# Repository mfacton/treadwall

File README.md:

# treadwall
Electronics for lightable rotating rockwall

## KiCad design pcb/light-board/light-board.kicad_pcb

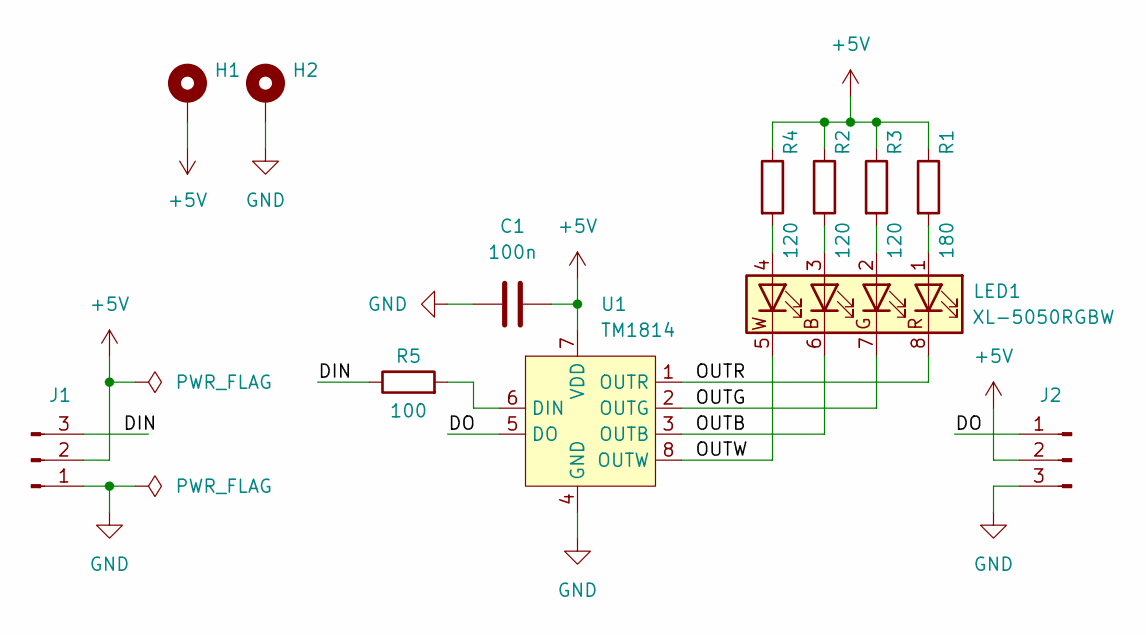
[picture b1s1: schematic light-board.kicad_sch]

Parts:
C1: 100n; C_0402_1005Metric; LCSC C1525
H1, H2: MountingHole_Pad; MountingHole_3.2mm_M3_Pad
J1, J2: Conn_01x03_Pin; JST_PH_S3B-PH-K_1x03_P2.00mm_Horizontal; LCSC C157929
LED1: XL-5050RGBW; LCSC C7371891
R1: 180; R_0603_1608Metric; LCSC C22828
R2, R3, R4: 120; R_0603_1608Metric; LCSC C22787
R5: 100; R_0402_1005Metric; LCSC C25076
U1: TM1814; SOP-8_3.9x4.9mm_P1.27mm; LCSC C20622183

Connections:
+5V: C1.2, H1.1, J1.2, J2.2, R1.1, R2.1, R3.1, R4.1, U1.7 (VDD)
/DIN: J1.3, R5.1
/DO: J2.1, U1.5 (DO)
/OUTB: LED1.6 (BK), U1.3 (OUTB)
/OUTG: LED1.7 (GK), U1.2 (OUTG)
/OUTR: LED1.8 (RK), U1.1 (OUTR)
/OUTW: LED1.5 (WK), U1.8 (OUTW)
GND: C1.1, H2.1, J1.1, J2.3, U1.4 (GND)
unnamed: LED1.3 (BA), R2.2
unnamed: LED1.2 (GA), R3.2
unnamed: LED1.1 (RA), R1.2
unnamed: LED1.4 (WA), R4.2
unnamed: R5.2, U1.6 (DIN)

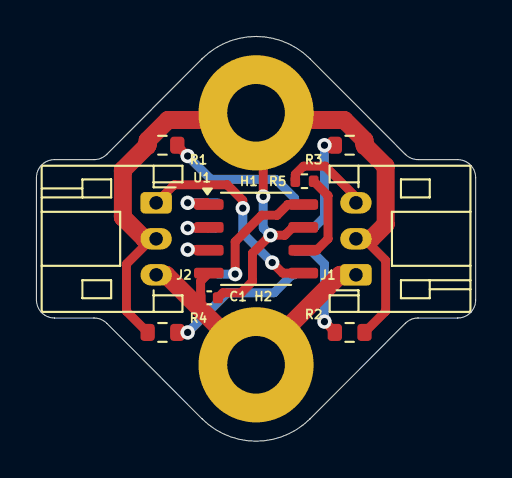
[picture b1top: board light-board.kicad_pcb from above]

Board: 2 copper layers, 24.4 x 22.5 mm, 12 parts (1 on the bottom side), 13 nets.

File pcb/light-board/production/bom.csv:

Designator,Footprint,Quantity,Value,LCSC Part #
C1,0402,1,100n,C1525
"J1, J2",JST_PH_S3B-PH-K_1x03_P2.00mm_Horizontal,2,Conn_01x03_Pin,C157929
LED1,XL-5050RGBW,1,XL-5050RGBW,C7371891
R1,0603,1,180,C22828
"R2, R3, R4",0603,3,120,C22787
R5,0402,1,100,C25076
U1,SOP-8_3.9x4.9mm_P1.27mm,1,TM1814,C20622183

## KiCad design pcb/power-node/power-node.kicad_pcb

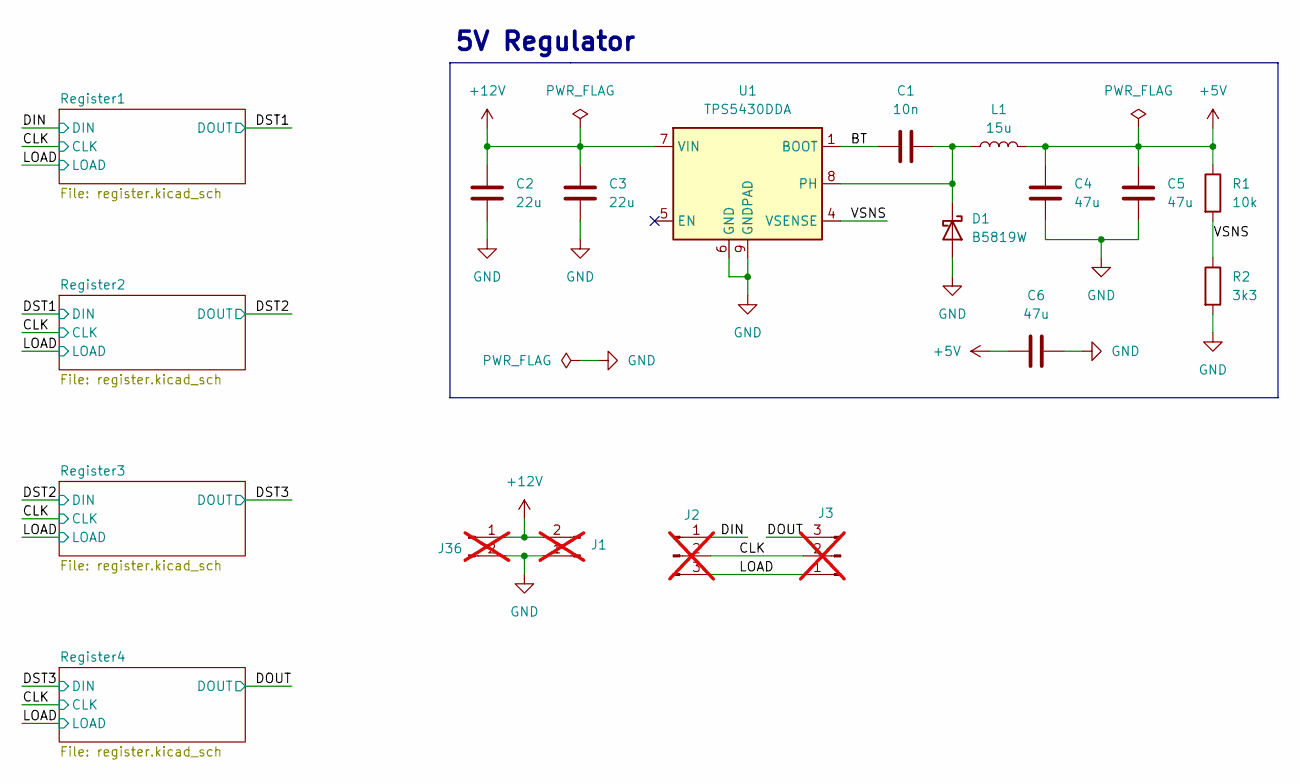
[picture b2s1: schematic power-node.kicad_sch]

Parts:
C1: 10n; C_0402_1005Metric; LCSC C15195
C2, C3: 22u; C_1206_3216Metric; LCSC C12891
C4, C5, C6: 47u; C_1206_3216Metric; LCSC C96123
D1: B5819W; D_SOD-123; LCSC C8598
J1, J36: Conn_01x02_Pin; WJ126V-5.0-2P; LCSC C8404; not fitted
J2, J3: Conn_01x03_Pin; PinHeader_1x03_P2.54mm_Vertical; not fitted
L1: 15u; L_Abracon_ASPI-0630LR; LCSC C177243
R1: 10k; R_0402_1005Metric; LCSC C25744
R2: 3k3; R_0402_1005Metric; LCSC C25890
U1: TPS5430DDA; TI_SO-PowerPAD-8_ThermalVias; LCSC C9864

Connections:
+5V: C4.1, C5.1, C6.1, L1.2, R1.1; also elsewhere on the board
+12V: C2.1, C3.1, J1.2, J36.1, U1.7 (VIN)
/BT: C1.1, U1.1 (BOOT)
/CLK: J2.2, J3.2; also elsewhere on the board
/DIN: J2.1; also elsewhere on the board
/DOUT: J3.3; also elsewhere on the board
/LOAD: J2.3, J3.1; also elsewhere on the board
/VSNS: R1.2, R2.1, U1.4 (VSENSE)
GND: C2.2, C3.2, C4.2, C5.2, C6.2, D1.2 (A), J1.1, J36.2, R2.2, U1.6 (GND), U1.9 (GNDPAD); also elsewhere on the board
unnamed: C1.2, D1.1 (K), L1.1, U1.8 (PH)

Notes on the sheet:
5V Regulator

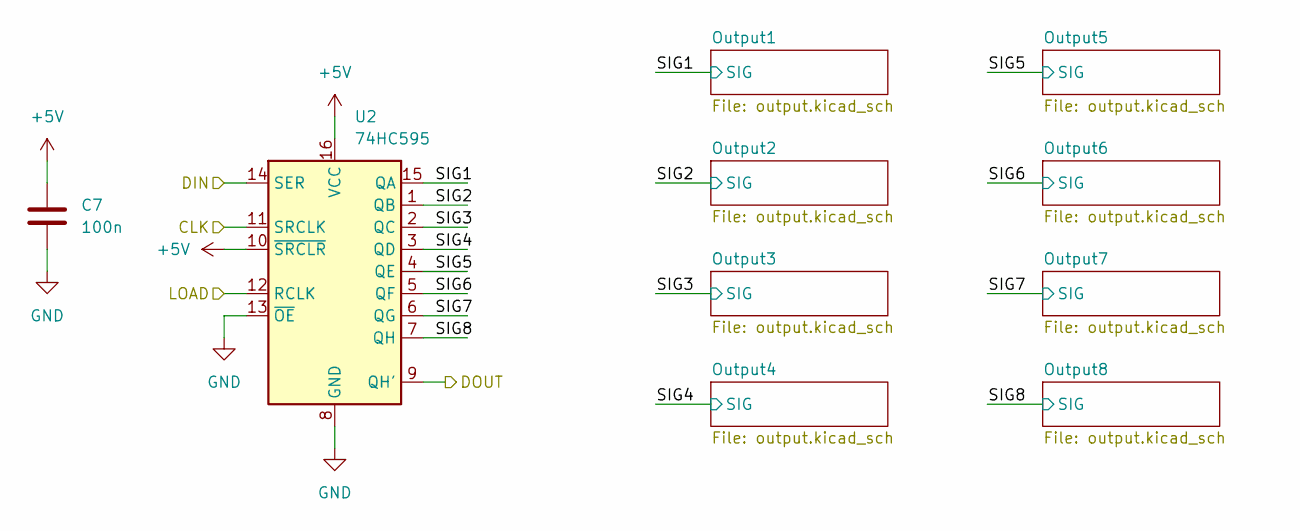
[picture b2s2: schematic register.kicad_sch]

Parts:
C7: 100n; C_0402_1005Metric; LCSC C1525
U2: 74HC595; SOIC-16_3.9x9.9mm_P1.27mm; LCSC C5947

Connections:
+5V: C7.1, U2.10 (~SRCLR), U2.16 (VCC); also elsewhere on the board
/CLK: U2.11 (SRCLK); also elsewhere on the board
/DIN: U2.14 (SER); also elsewhere on the board
/DST1: U2.9 (QH'); also elsewhere on the board
/LOAD: U2.12 (RCLK); also elsewhere on the board
/Register1/SIG1: U2.15 (QA); also elsewhere on the board
/Register1/SIG2: U2.1 (QB); also elsewhere on the board
/Register1/SIG3: U2.2 (QC); also elsewhere on the board
/Register1/SIG4: U2.3 (QD); also elsewhere on the board
/Register1/SIG5: U2.4 (QE); also elsewhere on the board
/Register1/SIG6: U2.5 (QF); also elsewhere on the board
/Register1/SIG7: U2.6 (QG); also elsewhere on the board
/Register1/SIG8: U2.7 (QH); also elsewhere on the board
GND: C7.2, U2.8 (GND), U2.13 (~OE); also elsewhere on the board

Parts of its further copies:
C8, C9, C10: 100n; C_0402_1005Metric; LCSC C1525
U3, U4, U5: 74HC595; SOIC-16_3.9x9.9mm_P1.27mm; LCSC C5947

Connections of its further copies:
+5V: C8.1, C9.1, C10.1, U3.10 (~SRCLR), U3.16 (VCC), U4.10 (~SRCLR), U4.16 (VCC), U5.10 (~SRCLR), U5.16 (VCC); also elsewhere on the board
/CLK: U3.11 (SRCLK), U4.11 (SRCLK), U5.11 (SRCLK); also elsewhere on the board
/DOUT: U5.9 (QH'); also elsewhere on the board
/DST1: U3.14 (SER); also elsewhere on the board
/DST2: U3.9 (QH'), U4.14 (SER)
/DST3: U4.9 (QH'), U5.14 (SER)
/LOAD: U3.12 (RCLK), U4.12 (RCLK), U5.12 (RCLK); also elsewhere on the board
/Register2/SIG1: U3.15 (QA); also elsewhere on the board
/Register2/SIG2: U3.1 (QB); also elsewhere on the board
/Register2/SIG3: U3.2 (QC); also elsewhere on the board
/Register2/SIG4: U3.3 (QD); also elsewhere on the board
/Register2/SIG5: U3.4 (QE); also elsewhere on the board
/Register2/SIG6: U3.5 (QF); also elsewhere on the board
/Register2/SIG7: U3.6 (QG); also elsewhere on the board
/Register2/SIG8: U3.7 (QH); also elsewhere on the board
/Register3/SIG1: U4.15 (QA); also elsewhere on the board
/Register3/SIG2: U4.1 (QB); also elsewhere on the board
/Register3/SIG3: U4.2 (QC); also elsewhere on the board
/Register3/SIG4: U4.3 (QD); also elsewhere on the board
/Register3/SIG5: U4.4 (QE); also elsewhere on the board
/Register3/SIG6: U4.5 (QF); also elsewhere on the board
/Register3/SIG7: U4.6 (QG); also elsewhere on the board
/Register3/SIG8: U4.7 (QH); also elsewhere on the board
/Register4/SIG1: U5.15 (QA); also elsewhere on the board
/Register4/SIG2: U5.1 (QB); also elsewhere on the board
/Register4/SIG3: U5.2 (QC); also elsewhere on the board
/Register4/SIG4: U5.3 (QD); also elsewhere on the board
/Register4/SIG5: U5.4 (QE); also elsewhere on the board
/Register4/SIG6: U5.5 (QF); also elsewhere on the board
/Register4/SIG7: U5.6 (QG); also elsewhere on the board
/Register4/SIG8: U5.7 (QH); also elsewhere on the board
GND: C8.2, C9.2, C10.2, U3.8 (GND), U3.13 (~OE), U4.8 (GND), U4.13 (~OE), U5.8 (GND), U5.13 (~OE); also elsewhere on the board

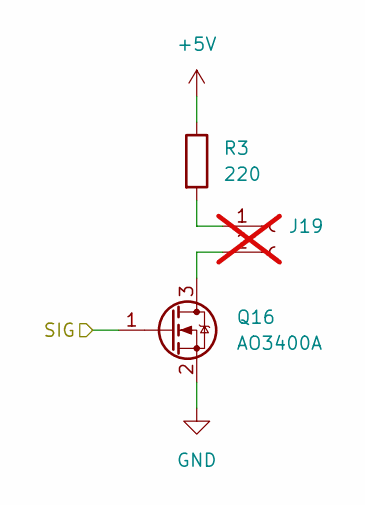
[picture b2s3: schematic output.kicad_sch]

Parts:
J19: Conn_01x02_Socket; PinHeader_1x02_P2.54mm_Vertical; not fitted
Q16: AO3400A; SOT-23; LCSC C20917
R3: 220; R_0603_1608Metric; LCSC C22962

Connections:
+5V: R3.1; also elsewhere on the board
/Register2/SIG3: Q16.1 (G); also elsewhere on the board
GND: Q16.2 (S); also elsewhere on the board
unnamed: J19.2, Q16.3 (D)

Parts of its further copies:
J4, J5, J6, J7, J8, J9, J10, J11, J12, J13, J14, J15, J16, J17, J18, J20, J21, J22, J23, J24, J25, J26, J27, J28, J29, J30, J31, J32, J33, J34, J35: Conn_01x02_Socket; PinHeader_1x02_P2.54mm_Vertical; not fitted
Q1, Q2, Q3, Q4, Q5, Q6, Q7, Q8, Q9, Q10, Q11, Q12, Q13, Q14, Q15, Q17, Q18, Q19, Q20, Q21, Q22, Q23, Q24, Q25, Q26, Q27, Q28, Q29, Q30, Q31, Q32: AO3400A; SOT-23; LCSC C20917
R4, R5, R6, R7, R8, R9, R10, R11, R12, R13, R14, R15, R16, R17, R18, R19, R20, R21, R22, R23, R24, R25, R26, R27, R28, R29, R30, R31, R32, R33, R34: 220; R_0603_1608Metric; LCSC C22962

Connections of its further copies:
+5V: R4.1, R5.1, R6.1, R7.1, R8.1, R9.1, R10.1, R11.1, R12.1, R13.1, R14.1, R15.1, R16.1, R17.1, R18.1, R19.1, R20.1, R21.1, R22.1, R23.1, R24.1, R25.1, R26.1, R27.1, R28.1, R29.1, R30.1, R31.1, R32.1, R33.1, R34.1; also elsewhere on the board
/Register1/SIG1: Q1.1 (G); also elsewhere on the board
/Register1/SIG2: Q2.1 (G); also elsewhere on the board
/Register1/SIG3: Q3.1 (G); also elsewhere on the board
/Register1/SIG4: Q4.1 (G); also elsewhere on the board
/Register1/SIG5: Q5.1 (G); also elsewhere on the board
/Register1/SIG6: Q6.1 (G); also elsewhere on the board
/Register1/SIG7: Q7.1 (G); also elsewhere on the board
/Register1/SIG8: Q8.1 (G); also elsewhere on the board
/Register2/SIG1: Q11.1 (G); also elsewhere on the board
/Register2/SIG2: Q12.1 (G); also elsewhere on the board
/Register2/SIG4: Q15.1 (G); also elsewhere on the board
/Register2/SIG5: Q14.1 (G); also elsewhere on the board
/Register2/SIG6: Q13.1 (G); also elsewhere on the board
/Register2/SIG7: Q10.1 (G); also elsewhere on the board
/Register2/SIG8: Q9.1 (G); also elsewhere on the board
/Register3/SIG1: Q19.1 (G); also elsewhere on the board
/Register3/SIG2: Q20.1 (G); also elsewhere on the board
/Register3/SIG3: Q24.1 (G); also elsewhere on the board
/Register3/SIG4: Q23.1 (G); also elsewhere on the board
/Register3/SIG5: Q22.1 (G); also elsewhere on the board
/Register3/SIG6: Q21.1 (G); also elsewhere on the board
/Register3/SIG7: Q18.1 (G); also elsewhere on the board
/Register3/SIG8: Q17.1 (G); also elsewhere on the board
/Register4/SIG1: Q27.1 (G); also elsewhere on the board
/Register4/SIG2: Q28.1 (G); also elsewhere on the board
/Register4/SIG3: Q32.1 (G); also elsewhere on the board
/Register4/SIG4: Q31.1 (G); also elsewhere on the board
/Register4/SIG5: Q30.1 (G); also elsewhere on the board
/Register4/SIG6: Q29.1 (G); also elsewhere on the board
/Register4/SIG7: Q26.1 (G); also elsewhere on the board
/Register4/SIG8: Q25.1 (G); also elsewhere on the board
GND: Q1.2 (S), Q2.2 (S), Q3.2 (S), Q4.2 (S), Q5.2 (S), Q6.2 (S), Q7.2 (S), Q8.2 (S), Q9.2 (S), Q10.2 (S), Q11.2 (S), Q12.2 (S), Q13.2 (S), Q14.2 (S), Q15.2 (S), Q17.2 (S), Q18.2 (S), Q19.2 (S), Q20.2 (S), Q21.2 (S), Q22.2 (S), Q23.2 (S), Q24.2 (S), Q25.2 (S), Q26.2 (S), Q27.2 (S), Q28.2 (S), Q29.2 (S), Q30.2 (S), Q31.2 (S), Q32.2 (S); also elsewhere on the board
unnamed: J4.2, Q1.3 (D)
unnamed: J5.1, R4.2
unnamed: J5.2, Q2.3 (D)
unnamed: J6.1, R5.2
unnamed: J6.2, Q3.3 (D)
unnamed: J7.1, R6.2
unnamed: J7.2, Q4.3 (D)
unnamed: J8.1, R7.2
unnamed: J8.2, Q5.3 (D)
unnamed: J9.1, R8.2
unnamed: J9.2, Q6.3 (D)
unnamed: J10.1, R9.2
unnamed: J10.2, Q7.3 (D)
unnamed: J11.1, R10.2
unnamed: J11.2, Q8.3 (D)
unnamed: J12.1, R11.2
unnamed: J12.2, Q9.3 (D)
unnamed: J13.1, R12.2
unnamed: J13.2, Q10.3 (D)
unnamed: J14.1, R13.2
unnamed: J14.2, Q11.3 (D)
unnamed: J15.1, R14.2
unnamed: J15.2, Q12.3 (D)
unnamed: J16.1, R15.2
unnamed: J16.2, Q13.3 (D)
unnamed: J17.1, R16.2
unnamed: J17.2, Q14.3 (D)
unnamed: J18.1, R17.2
unnamed: J18.2, Q15.3 (D)
unnamed: J20.1, R19.2
unnamed: J20.2, Q17.3 (D)
unnamed: J21.1, R20.2
unnamed: J21.2, Q18.3 (D)
unnamed: J22.1, R21.2
unnamed: J22.2, Q19.3 (D)
unnamed: J23.1, R22.2
unnamed: J23.2, Q20.3 (D)
unnamed: J24.1, R23.2
unnamed: J24.2, Q21.3 (D)
unnamed: J25.1, R24.2
unnamed: J25.2, Q22.3 (D)
unnamed: J26.1, R25.2
unnamed: J26.2, Q23.3 (D)
unnamed: J27.1, R26.2
unnamed: J27.2, Q24.3 (D)
unnamed: J28.1, R27.2
unnamed: J28.2, Q25.3 (D)
unnamed: J29.1, R28.2
unnamed: J29.2, Q26.3 (D)
unnamed: J30.1, R29.2
unnamed: J30.2, Q27.3 (D)
unnamed: J31.1, R30.2
unnamed: J31.2, Q28.3 (D)
unnamed: J32.1, R31.2
unnamed: J32.2, Q29.3 (D)
unnamed: J33.1, R32.2
unnamed: J33.2, Q30.3 (D)
unnamed: J34.1, R33.2
unnamed: J34.2, Q31.3 (D)
unnamed: J35.1, R34.2
unnamed: J35.2, Q32.3 (D)

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
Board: 2 copper layers, 119 parts (0 on the bottom side), 109 nets, no tracks yet.

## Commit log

2024-07-11 Initial design notes
2024-07-11 Create initial schematic
2024-07-15 Add cost prediction notes
2024-07-15 Finish pcb for production
2024-09-04 Ignore stm32 files
2024-09-04 Save progress
